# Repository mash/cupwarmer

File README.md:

# cupwarmer

Qi ワイヤレス給電で飲み物を温かく保つ、カップウォーマーの自作プロジェクトです。カップの下に置く小さなデバイスに、Qi 受電回路・ヒーター・温度保護をまとめています。

目標は **15W 級の Qi EPP 受電と、12V・約12W のヒーター**。保温と軽い再加熱を狙って開発しています。

## 構成

| 部分 | v1 の設計 |
| --- | --- |
| Qi 受電 | STMicroelectronics STWLC38JRM。外部 MCU を使わず、IC の自律動作を利用 |
| 制御 PCB | 直径50mm、4層、厚さ1.6mm |
| ヒーター | 直径約55mm のシリコーン flexible heater。12Ω、100kΩ NTC 内蔵 |
| 温度保護 | heater 内蔵 NTC を STWLC38 の `RX_NTC` に接続。独立した70°C サーモスタット F1 をヒーターに直列接続 |
| メンテナンス | I²C service header から状態確認・NVM 設定 |
| 筐体 | 外径60mm の bottom tray。OpenSCAD で設計 |

カップ側から **cup contact pad → flexible heater → insulation → PCB → ferrite → RX coil → bottom tray** の順に重ねます。aluminum spreader は比較候補で、初回評価では省く構成です。

### 基板

### Qi 受電回路

### ヒーター回路

v1 は受電出力が有効な間、ヒーターを連続通電する設計です。PWM による温度調整は実装していません。

画像は設計の概要を示すスクリーンショットです。製作・変更時は [KiCad ソース](hardware/kicad/) と [機構ソース](hardware/mechanical/enclosure-proto.scad) を参照してください。機構図には比較候補の部材も含まれます。

## 開発状況

**動作・温度保護を評価中の試作です。**

確認済み:

- PCB とヒーターを受領。ヒーターの抵抗、NTC の温度応答、電力線とセンサー線の絶縁を確認。
- CP2112 とレベル変換基板を使った I²C 通信、STWLC38 の NVM 書き込み・読み戻しを確認。
- patch 1656 と試作設定 DA04 の保持、および電源再投入後の室温での Qi 起動を確認。

未検証:

- 実際のカップを使った加熱・保温性能と、EPP 12V での負荷動作。
- NTC の実際の遮断温度、出力停止、復帰動作。DA04 は温度保護の検証を終えた設定ではありません。
- 組み上げた状態での異物検出（FOD）、位置ずれ、空焼き時の挙動。

直近の DA04 試験はヒーター電源線を切り離した状態で行っています。12V・約12W は設計目標であり、達成済みの性能ではありません。試験条件と結果は [DA04 を含む NVM 設定の記録](hardware/test/2026-10-04-stwlc38-da01-programming.md) にまとめています。

## リポジトリの内容

| 場所 | 内容 |
| --- | --- |
| [docs/design-notes.md](docs/design-notes.md) | 設計判断と評価方針 |
| [hardware/kicad/](hardware/kicad/) | 回路図・PCB・部品ライブラリ |
| [hardware/bom/](hardware/bom/) | 部品表と実装発注用 BOM |
| [hardware/fab/](hardware/fab/) | Gerber・部品配置などの製造出力 |
| [hardware/mechanical/](hardware/mechanical/) | OpenSCAD モデル・STL・機構設計ノート |
| [hardware/firmware/stwlc38/](hardware/firmware/stwlc38/) | ST 参照ファームウェア・設定と取得元 |
| [hardware/test/](hardware/test/) | 試験記録・設定候補・I²C ツール・オフラインテスト |
| [wiki/](wiki/) | 部品・規格・参考資料の調査ノート |

詳しい機構構成は [機構設計ノート](hardware/mechanical/README.md)、NVM 書き込みの手順と制約は [STWLC38 programming](hardware/test/stwlc38-programming.md) を参照してください。

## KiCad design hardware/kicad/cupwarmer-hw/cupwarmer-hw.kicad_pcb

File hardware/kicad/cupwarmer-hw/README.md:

# cupwarmer-hw

KiCad 10 向けの初回プロジェクト雛形。

## 含まれるもの

- `cupwarmer-hw.kicad_pro`
- `cupwarmer-hw.kicad_sch`
- `cupwarmer-hw.kicad_pcb`

## 方針

- まず KiCad で開ける最小プロジェクトを置く
- `STWLC38JRM` 周辺の具体回路は次段階で回路図へ入れる
- 既存の設計メモは以下を参照
  - `../../schematic/README.md`
  - `../../pcb/README.md`
  - `../../../docs/design-notes.md`

## 次にやること

1. `floorplan-v1.md` の zone に沿って主要部品を placement する
2. actual coil / ferrite geometry で placeholder guide を置き換える
3. PCB DRC と schematic parity を通す

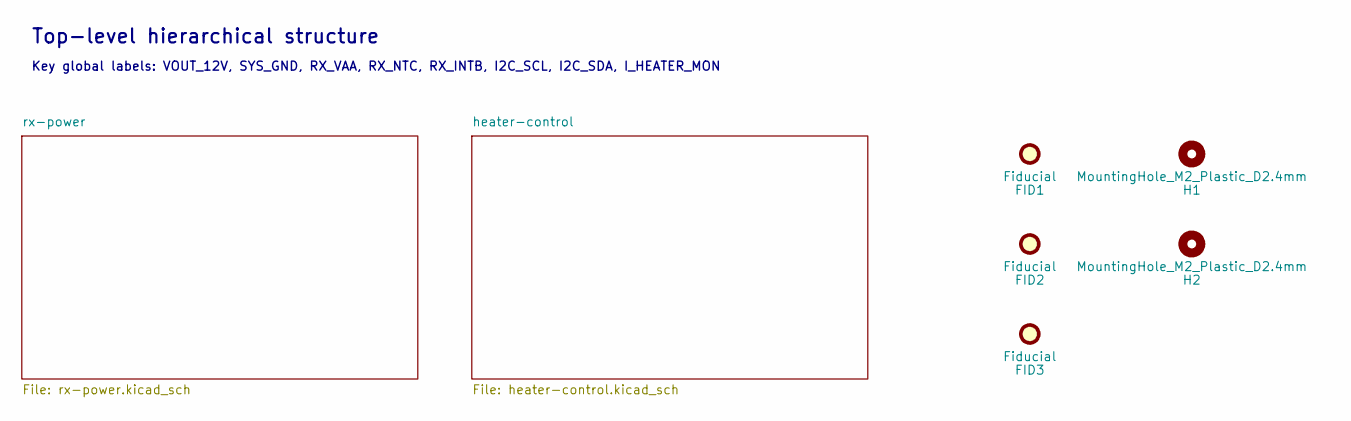
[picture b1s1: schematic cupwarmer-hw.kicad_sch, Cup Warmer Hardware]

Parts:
FID1, FID2, FID3: Fiducial; Fiducial_1mm_Mask3mm
H1, H2: MountingHole_M2_Plastic_D2.4mm

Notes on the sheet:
Top-level hierarchical structure
Key global labels: VOUT_12V, SYS_GND, RX_VAA, RX_NTC, RX_INTB, I2C_SCL, I2C_SDA, I_HEATER_MON

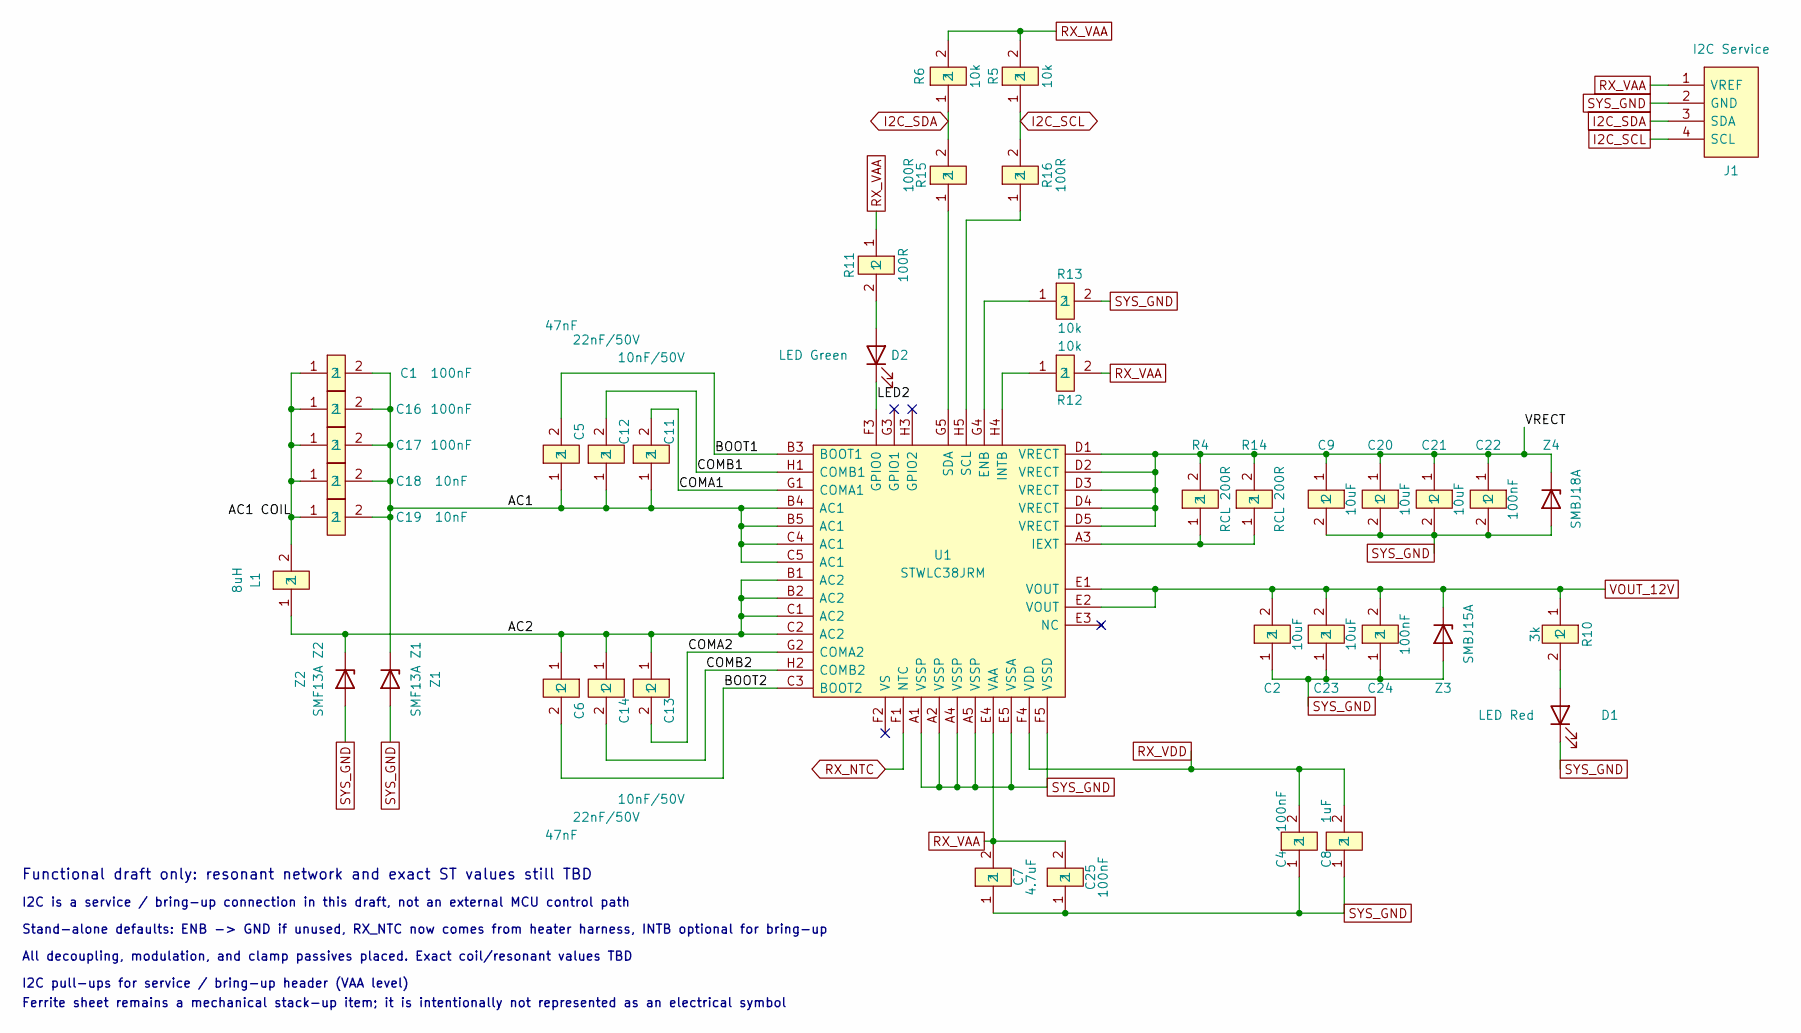
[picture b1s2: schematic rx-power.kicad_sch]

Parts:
C1, C16, C17: 100nF; C_1206_3216Metric; MPN GRM31C5C1H104JA01L; LCSC C97946
C2, C9, C20, C21, C23: 10uF; C_0603_1608Metric; MPN GRM188R6YA106MA73D; LCSC C194427
C4, C22, C24, C25: 100nF; C_0603_1608Metric; MPN 885012206095; LCSC C6715111
C5, C6: 47nF; C_0603_1608Metric; MPN CL10B473KB8NNNC; LCSC C1622
C7: 4.7uF; C_0603_1608Metric; MPN GRM188R61E475KE11D; LCSC C90057
C8: 1uF; C_0603_1608Metric; MPN CL10A105KB8NNNC; LCSC C15849
C11, C13: 10nF/50V; C_0603_1608Metric; MPN GRM1885C1H103JA01D; LCSC C85973
C12, C14: 22nF/50V; C_0603_1608Metric; MPN CL10B223KB8NNNC; LCSC C21122
C18, C19: 10nF; C_0603_1608Metric; MPN GRM1885C1H103JA01D; LCSC C85973
D1: LED Red; LED_0603_1608Metric
D2: LED Green; LED_0603_1608Metric
J1: I2C Service; PinHeader_1x04_P2.54mm_Vertical; MPN PZ254V-11-04P; LCSC C2691448
L1: 8uH; SolderWire-Wuerth760308_1x02_P5.0mm_D1.2mm; MPN 760308102207
R4, R14: RCL 200R; R_0805_2012Metric; MPN ERJP06F2000V; LCSC C543538
R5, R6, R12, R13: 10k; R_0603_1608Metric; MPN 0603WAF1002T5E; LCSC C25804
R10: 3k; R_0603_1608Metric; MPN 0603WAF3001T5E; LCSC C4211
R11, R15, R16: 100R; R_0603_1608Metric; MPN 0603WAF1000T5E; LCSC C22775
U1: STWLC38JRM; STWLC38JRM_WLCSP40; MPN STWLC38JRM; LCSC C5267845
Z1: SMF13A Z1; D_SOD-123F; MPN SMF13A; LCSC C353315
Z2: SMF13A Z2; D_SOD-123F; MPN SMF13A; LCSC C353315
Z3: SMBJ15A; D_SMB_Pin1K; MPN SMBJ15A; LCSC C83846
Z4: SMBJ18A; D_SMB_Pin1K; MPN SMBJ18A; LCSC C19077573

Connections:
/rx-power/AC1: C1.2, C5.1, C11.1, C12.1, C16.2, C17.2, C18.2, C19.2, U1.B4 (AC1), U1.B5 (AC1), U1.C4 (AC1), U1.C5 (AC1), Z1.1 (K)
/rx-power/AC1 COIL: C1.1, C16.1, C17.1, C18.1, C19.1, L1.2
/rx-power/AC2: C6.1, C13.1, C14.1, L1.1, U1.B1 (AC2), U1.B2 (AC2), U1.C1 (AC2), U1.C2 (AC2), Z2.1 (K)
/rx-power/BOOT1: C5.2, U1.B3 (BOOT1)
/rx-power/BOOT2: C6.2, U1.C3 (BOOT2)
/rx-power/COMA1: C11.2, U1.G1 (COMA1)
/rx-power/COMA2: C13.2, U1.G2 (COMA2)
/rx-power/COMB1: C12.2, U1.H1 (COMB1)
/rx-power/COMB2: C14.2, U1.H2 (COMB2)
/rx-power/LED2: D2.1 (K), U1.F3 (GPIO0)
/rx-power/VRECT: C9.1, C20.1, C21.1, C22.1, R4.2, R14.2, U1.D1 (VRECT), U1.D2 (VRECT), U1.D3 (VRECT), U1.D4 (VRECT), U1.D5 (VRECT), Z4.1 (K)
I2C_SCL: J1.4 (SCL), R5.1, R16.2
I2C_SDA: J1.3 (SDA), R6.1, R15.2
unnamed: D1.2 (A), R10.2
unnamed: D2.2 (A), R11.2
unnamed: R13.1, U1.G4 (ENB)
unnamed: R4.1, R14.1, U1.A3 (IEXT)
unnamed: R12.1, U1.H4 (INTB)
unnamed: R16.1, U1.H5 (SCL)
unnamed: R15.1, U1.G5 (SDA)
RX_NTC: U1.F1 (NTC); also elsewhere on the board
RX_VAA: C7.2, C25.2, J1.1 (VREF), R5.2, R6.2, R11.1, R12.2, U1.E4 (VAA); also elsewhere on the board
RX_VDD: C4.2, C8.2, U1.F4 (VDD)
SYS_GND: C2.1, C4.1, C7.1, C8.1, C9.2, C20.2, C21.2, C22.2, C23.1, C24.1, C25.1, D1.1 (K), J1.2 (GND), R13.2, U1.A1 (VSSP), U1.A2 (VSSP), U1.A4 (VSSP), U1.A5 (VSSP), U1.E5 (VSSA), U1.F5 (VSSD), Z1.2 (A), Z2.2 (A), Z3.2 (A), Z4.2 (A); also elsewhere on the board
VOUT_12V: C2.2, C23.2, C24.2, R10.1, U1.E1 (VOUT), U1.E2 (VOUT), Z3.1 (K); also elsewhere on the board

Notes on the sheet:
Functional draft only: resonant network and exact ST values still TBD
I2C is a service / bring-up connection in this draft, not an external MCU control path
Stand-alone defaults: ENB -> GND if unused, RX_NTC now comes from heater harness, INTB optional for bring-up
All decoupling, modulation, and clamp passives placed. Exact coil/resonant values TBD
I2C pull-ups for service / bring-up header (VAA level)
Ferrite sheet remains a mechanical stack-up item; it is intentionally not represented as an electrical symbol

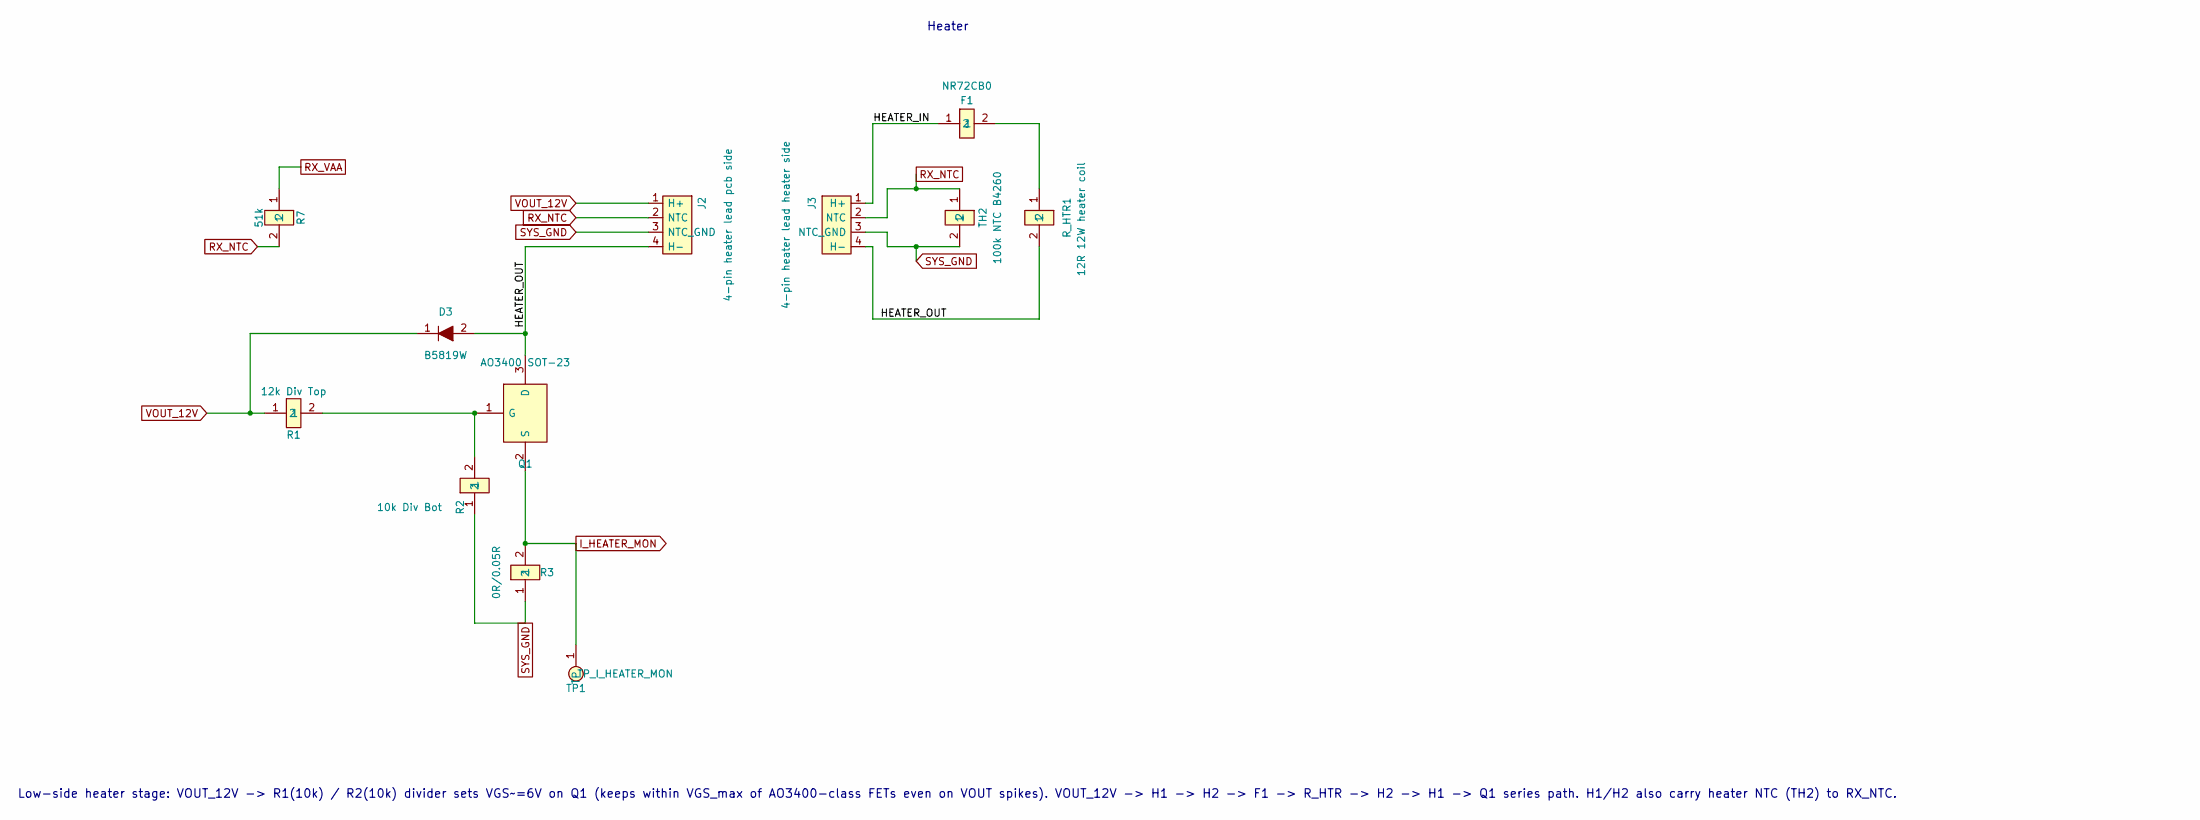
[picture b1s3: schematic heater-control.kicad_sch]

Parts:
D3: B5819W; D_SOD-123; MPN B5819W; LCSC C8598
F1: NR72CB0; MPN NR72CB0; LCSC C183007
J2: 4-pin heater lead pcb side; SolderWire-HeaterHarness_1x04_P5.0mm_D1.4mm
J3: 4-pin heater lead heater side; SolderWire-HeaterHarness_1x04_P5.0mm_D1.4mm
Q1: AO3400 SOT-23; SOT-23; MPN AO3400; LCSC C181090
R1: 12k Div Top; R_0603_1608Metric; MPN 0603WAF1202T5E; LCSC C22790
R2: 10k Div Bot; R_0603_1608Metric; MPN 0603WAF1002T5E; LCSC C25804
R3: 0R/0.05R; R_1206_3216Metric; MPN FRM121WFR050TM; LCSC C7467249
R7: 51k; R_0603_1608Metric; MPN 0603WAF5102T5E; LCSC C23196
R_HTR1: 12R 12W heater coil
TH2: 100k NTC B4260
TP1: TP_I_HEATER_MON; PinHeader_1x01_P2.54mm_Vertical

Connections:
/heater-control/HEATER_OUT: D3.2 (A), J2.4 (H-), J3.4 (H-), Q1.3 (D), R_HTR1.2
I_HEATER_MON: Q1.2 (S), R3.2, TP1.1 (TP_1)
unnamed: F1.1, J3.1 (H+)
unnamed: F1.2, R_HTR1.1
unnamed: Q1.1 (G), R1.2, R2.2
RX_NTC: J2.2 (NTC), J3.2 (NTC), R7.2, TH2.1; also elsewhere on the board
RX_VAA: R7.1; also elsewhere on the board
SYS_GND: J2.3 (NTC_GND), J3.3 (NTC_GND), R2.1, R3.1, TH2.2; also elsewhere on the board
VOUT_12V: D3.1 (K), J2.1 (H+), R1.1; also elsewhere on the board

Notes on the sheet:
Low-side heater stage: VOUT_12V -> R1(10k) / R2(10k) divider sets VGS~=6V on Q1 (keeps within VGS_max of AO3400-class FETs even on VOUT spikes). VOUT_12V -> H1 -> H2 -> F1 -> R_HTR -> H2 -> H1 -> Q1 series path. H1/H2 also carry heater NTC (TH2) to RX_NTC.
Heater

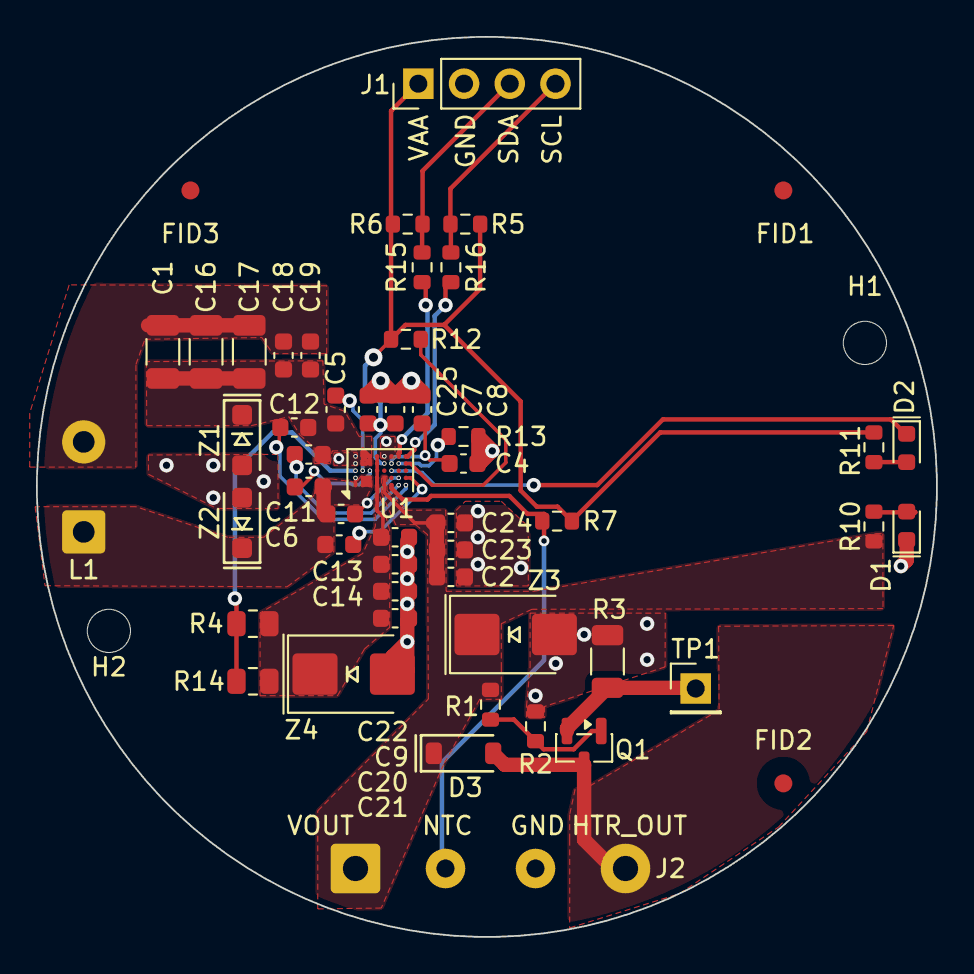
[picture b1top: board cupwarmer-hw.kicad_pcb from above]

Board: 4 copper layers, 50.0 x 50.0 mm, 54 parts (0 on the bottom side), 28 nets.

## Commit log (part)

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2026-04-11 initial
2026-04-12 Add STEVAL-WLC38RX wiki reference files
2026-04-12 Refactor KiCad editing skills
2026-04-12 Ignore Python bytecode caches
2026-04-17 Move skills into .agents and update text collision detection
2026-04-17 Update hardware schematics and BOM
2026-04-17 Ignore KiCad local project files
2026-04-18 Add KiCad layout optimization skill
2026-04-18 Optimize rx-power schematic layout
2026-04-19 Fix KiCad schematic connectivity and symbol sync
2026-04-25 Improve schematic layout clearance scoring
2026-04-25 Refine KiCad schematic layout
2026-04-25 Penalize schematic label pin conflicts
2026-04-25 Remove KiCad layout optimize skill
2026-04-25 Remove schematic edit skill
2026-04-26 Refactor KiCad skills around unified tool
2026-04-26 Improve KiCad inspect layout metrics
2026-04-26 Clean up sensors logic schematic layout
2026-04-26 Improve rx power NTC schematic layout
2026-04-26 Clean up rx power label layout
2026-04-26 Route rx power C2 net around symbol
2026-04-26 Improve KiCad layout cleanup guidance
2026-04-26 Add GPIO0 status LED to rx schematic
2026-04-28 Score schematic edge-hugging wires
2026-04-29 Update rx-power schematic: relocate C4 and R7, tidy SYS_GND connections
    Relocate C4 (100nF bypass) and R7 (10k NTC pull-up) within the rx-power
    schematic. Update SYS_GND label placement and adjust wiring to match
    the new component locations.
2026-04-29 Add `sch edit symbol move-property` for property placement edits
    This extends the repo-local `kicad-tool` CLI to relocate symbol fields like `Reference`/`Value` (and optional rotation) without moving the whole symbol.
    Made-with: Cursor
2026-04-29 Adjust label collision scoring
2026-04-29 Document thermal safety design
2026-04-29 Add VOUT TVS clamp
2026-04-29 Document bring-up constraints
2026-04-29 Document heater harness footprint
2026-05-02 Add v1 PCB floorplan and thermal bring-up notes
2026-05-02 Prepare v1 PCB placement planning
2026-05-04 ignore wiki
2026-05-05 Remove TH1 footprint from PCB
    TH1 was deleted from the schematic; reflect it on the PCB.
    NTC_TOP off-board sensing is dropped — TH2 (RX_NTC for STWLC38
    internal OTP) remains the only thermistor.
2026-05-05 Switch L1 to Würth 760308102207 (WE-WPCC 8 µH)
    AN5961 Table 1 L4 reference coil with published DCR/ACR
    (60 mΩ typ vs YX-A11 unspecified). Mouser/Digi-Key stocked,
    40×40×1.2 mm rounded-square fits within the φ56 mm PCB.
    YX-A11 retained as measurement-comparison candidate.
2026-05-05 Add `pcb edit footprint delete` to kicad-tool
    Needed to remove C15 footprint from cupwarmer-hw.kicad_pcb after
    deleting the Cd symbol from the schematic.
2026-05-05 Drop Cd (C15) parallel resonant cap
    UM3154 §9.1.2 documents Cd as optional, used only for Qi-cert
    backward compatibility with specific TX coils. cupwarmer is not
    pursuing Qi certification, so the cap adds drift and loss without
    benefit. Removed C15 (3.3 nF NP0 / Walsin 0603N332J500CT) from
    the rx-power schematic, the PCB, and the BOM. Decision recorded
    in docs/design-notes.md.
2026-05-05 Switch L1 footprint to Würth 760308102207 (P5.0mm)
    Custom SolderWire footprint with 5.0mm pitch and φ1.2mm holes
    matching the WE-WPCC 760308102207 lead pattern. Includes a
    40×40mm rounded-square outline on Dwgs.User as a placement guide
    for the coil module body. Schematic L1 properties (Value, MPN,
    Manufacturer, LCSC, Footprint) updated to match the BOM.
    ERC clean; PCB parity unchanged; no new DRC violations on L1.
2026-05-05 Actually drop C15 (Cd) symbol + footprint
    Earlier 522ecc1 commit removed the BOM row but the kicad-tool
    delete on the schematic silently no-op'd, leaving C15 in
    rx-power.kicad_sch and the PCB. This commit deletes the symbol,
    its two dangling wire stubs, and the footprint. ERC clean.
2026-05-05 Record Cs dielectric decision: C0G 0805 multi-parallel
    cup warmer is in continuous warm operation (heater H1 + coil losses), so
    X7R temperature drift (+/-15%) plus DC bias capacitance loss would shift
    the AC1/AC2 series resonance and degrade efficiency / VRECT regulation.
    C0G (NP0) is required.
    Smaller-is-better, but 100nF/50V C0G in 0603 does not exist as a standard
    stock part (C0G volumetric efficiency caps 0603 50V at ~22nF). Derating
2026-05-05 Set STWLC38 NTC pull-up to 51k
2026-05-05 Sync PCB values and remove unused monitor footprints
2026-05-05 Add parallel SOVP clamp resistors
2026-05-05 Change power indicator LED to red
2026-05-05 Add PCB layer list query
2026-05-05 Enable kicad-skills plugin in project settings
2026-05-06 Reposition U1 passives and add hole-to-hole DRC exclusions
    Rotate and shift the COMA/COMB and Cs decoupling caps around U1, nudge
    several breakout passives, and exclude a cluster of hole-to-hole DRC
    violations under U1's BGA escape area where via spacing is intentional.
2026-05-06 Rework SYS_GND segments around U1 and refresh DRC exclusions
    Replace the SYS_GND stub routing under U1 with cleaner short segments,
    nudge a couple of breakout pads, and refresh the hole-to-hole DRC
    exclusion list to match the new via positions.
2026-05-06 Replace coil/ferrite notes with BGA via fab note
    Drop the placeholder "NO LARGE METAL OVER COIL CORE" and "FERRITE /
    MECH ENVELOPE TBD" notes and add a Cmts.User note specifying that U1
    BGA escape vias (0.15mm drill / 0.25mm dia) must be epoxy-filled and
    copper-capped, with no open vias on BGA pads. Reposition the title
    block.
2026-05-06 Document ferrite sheet sourcing
2026-05-09 Add heater harness NTC routing
2026-05-09 Add VAA high-frequency bypass capacitor
2026-05-09 Update PCB layout state
    add C25
2026-05-11 Update UM3154 PCB layout state
2026-05-16 Tighten RX clamp layout and thermal notes
2026-05-16 Add coil body placement guide
2026-05-16 Lower heater gate divider voltage
2026-05-16 Document heater harness and LED decisions
2026-05-16 Add schematic mounting holes for board parity
2026-05-16 Remove unused status monitor header
2026-05-17 Document bring-up shunt and reset pad defaults
2026-05-17 Expand Q1 drain thermal pour
2026-05-17 Remove redundant NTC ground test point
2026-05-17 Swap service I2C header pins
2026-05-17 Increase coil ground isolation
2026-05-17 Fix LED polarity and heater flyback diode
2026-05-17 Fix D2 PCB orientation
2026-05-17 Move AC TVS clamps closer to receiver IC
2026-05-23 Update cupwarmer PCB fab outputs
2026-05-23 Allow U1 BGA escape via annular ring
2026-05-23 Sync PCB footprint properties
2026-05-24 Remove PCB mounting holes
2026-05-24 Add enclosure prototype mechanical model
2026-05-25 Update PCBA BOM and fabrication outputs
2026-05-31 Add DFM trace spacing DRC warnings
2026-05-31 Update PCB spacing DRC coverage
2026-05-31 Add through-hole to SMD spacing rule
2026-05-31 Update silkscreen DRC rules
2026-05-31 Add silkscreen to hole DRC rule
2026-05-31 Update PCB layout
2026-06-06 Fix TVS footprint parity
2026-06-06 DRC clean after 50mm resize: reconnect nets, relocate parts, add U1 same-net via escape rule
    - Reconnect RX_VAA/I2C_SDA/I2C_SCL tracks to moved J1 pads; drop dangling stubs
    - Move SYS_GND via inward to clear board edge; shift R10/R11 to clear D1/D2 courtyards
    - Restagger J1 (VAA/GND/SDA/SCL) and VOUT/HTR_OUT silk to clear edge/holes
    - Add "U1 BGA Escape Via Hole to Via Hole (Same Net)" .dru rule (min 0.2mm)
    so dense same-net SYS_GND stitching vias under U1 pass; rest of board stays 0.254mm
    - Result: 0 DRC violations, 0 unconnected
2026-06-06 Remove stale kicad-tool schematic-parity TODO plan
    Tracked in kicad-skills repo, not cupwarmer.
